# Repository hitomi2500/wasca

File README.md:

# wasca
wasca is a multipurpose Sega Saturn cartridge based on Lattice ECP5 FPGA with PicoRV32 RISC-V soft CPU core ([`picorv32`][2]). 

wasca can operate in several modes:

- Backup memory cartridge
- RAM expansion cartridge
- ROM cartridge
- Homebrew software compiled as a cartridge ROM 

> Netlink support is planned via an ESP32-CAM module connected to the 6-pin expansion header.

> Optical drive emulation (ODE) function is theoretically possible, but not planned currently.

> Profiling can be supported using a special firmware version, but it requires support from SH-2 code.

---

# Quick Start

1. Prepare the SD card formatted as FAT32. Other filesystems like NTFS and exFAT are not supported.
2. Copy `wasca.ss` and `wasca.rv` to the SD card root directory. Note that the file names should be in lowercase on the card, check FAT32 LFN support or reformat the card if they are not.
3. Insert the SD card into wasca, plug wasca into the cartridge slot, power on the console
4. Verify that the front LED on the cartridge turns red, then blue.
5. wasca menu should appear on screen after boot logo. Some ODEs can bypass wasca boot process entirely. In this case, consult your ODE documentation to learn how to return to cartridge boot mode after selecting a game.

---

# LED Status Reference

| Color | Meaning |
|---|---|
| Red | Reading SD card at startup or system error. |
| Red, blinking | Boot error, either `wasca.ss` and `wasca.rv` was not found on SD card, refer to on-screen error message. |
| Blue | Firmware found on SD card, boot successful, waiting for menu selection. |
| Green, blinking | Write access in RAM or Homebrew mode. |
| Magenta, blinking | Write access to backup memory in backup mode or filesystem write access. |
| Cyan, blinking | Massive write access to backup memory (happens during format) or filesystem read access. |
| Yellow, blinking | Preparing backup memory |
| White, blinking | Filesystem open, close, seek etc.|

---

# Backup Memory Support

wasca supports four backup memory sizes:

- 0.5 MB (official Sega Saturn size)
- 1 MB
- 2 MB
- 4 MB

If not already present, the following backup files are created automatically on the SD card when selected from the menu:

- `backup05.bin`
- `backup1.bin`
- `backup2.bin`
- `backup4.bin`

Syncronization is done automatically, led blinking with magenta color signals write access, led blinking with cyan signals massive write access and usually happens during cart format in BIOS.

---

# RAM Expansion Support

wasca supports these RAM expansion modes:

- 1 MB official RAM expansion (timings not 100% compatible)
- 4 MB official RAM expansion
- Heart of Darkness mode (HoD will work in homebrew mode as well)

---

# ROM Support

The following games require corresponding ROM files placed in the SD card root directory:

| Game | Required File |
|---|---|
| King of Fighters '95 | `kof95.bin` |
| Ultraman | `ultraman.bin` |

When present on SD card, ROM will appear in menu and should be selected prior to launching the game.

---

# Homebrew Support

Any Sega Saturn homebrew compiled for cartridge can be placed into the SD card root directory. `.ss` and `.bin` extensions are supported. wasca automatically scans and lists `.bin` and `.ss` files found in the SD card root directory.

In homebrew mode, wasca exposes:

- 32 MB of CS0 space
- 16 MB of CS1 space

These regions are available to the developer as RAM.

[`Yaul`][1] system library supports compiling sortware for cartridge with a special makefile include (build.post.ss.mk) that should be added to the project's Makefile instead of the default one (build.post.iso-cue.mk).

---

# Menu limit

Currently, wasca menu is limited to 18 items. If more `.bin` and `.ss` files that fit on screen are present in the SD card root, only first items will be shown. Use wasca commander (still under development) file manager to load extra files or files in non-root folders.

---

# Firmware update

wasca firmware consists of 3 parts:

- FPGA gateware: `attosoc.bit`
- RISC-V firmware: `wasca.rv`
- SH-2 firmware: `wasca.ss`

### Updating FPGA gateware

1. Disconnect wasca from the console
2. Remove two screws on the back of the cartridge
3. Open the cartridge shell
4. Connect wasca to PC using USB-C cable
5. A removable drive will appear
6. Copy `attosoc.bit` onto the drive
7. Wait for 2 minutes before disconnecting the cartridge
8. Assemble the cartridge and connect to the console.

### Updating RISC-V and SH-2 Firmware

1. Remove SD card from wasca
2. Replace the existing `wasca.rv` and `wasca.ss` files on the SD card with a newer version.
3. Re-insert the card. Console power cycle is necessary for wasca to load the new firmware.

---

# SD card removal
Removing the SD card when console is powered up is only recommended when the front LED is not lit and not blinking. Re-inserting the card without reset is possible if LED did not blink while the card was removed, but data integrity is not tested and not guaranteed.

---

# Troubleshooting

### Lit red LED and/or "wasca : boot error" on screen

Possible causes:
- Unsupported filesystem
- Bad SD card
- Unstable SD card connection

Try:
- Re-insert the SD card
- Reformat the SD card as FAT32
- Replace SD card

### Blinking red LED and/or missing file message on screen

Possible causes:
- Missing `wasca.ss` or `wasca.rv` in the SD card root
- Unsupported filesystem
- Bad SD card

Try:
- Verify that both `wasca.ss` and `wasca.rv` exists in the SD card root directory, named in lowercase
- Reformat the SD card as FAT32
- Replace the SD card

### Lit blue LED, wasca boot menu does not appear during boot

Possible causes:
- Poor cartridge connection
- Dirty cartridge connector
- ODE bypassing cartridge initialization

Try:
- Reseating the cartridge
- Cleaning the cartridge and connector
- Consulting your ODE documentation for cartridge boot instructions

### Game ROM of homebrew .ss file present in root folder, but does not appear in the menu

Possible causes:
- Too many files in SD card root
- Wrong charset

Try:
- Verify that there is enough place on the screen to print necessary menu item. If last menu item is 18, it's probably overfilled and extra items are not shown.
- Verify that the file extension is `.bin` or `.ss`, lowercase, latin1 characters.

[1]: https://github.com/ijacquez/libyaul
[2]: https://github.com/YosysHQ/picorv32

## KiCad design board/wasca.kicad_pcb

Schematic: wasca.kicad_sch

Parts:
C1, C2, C4, C5, C7, C9, C10, C11, C14, C15, C16, C17, C18, C19, C20, C21, C22, C23, C24, C25, C26, C27, C28, C33, C34, C35, C36, C37, C38, C39, C40, C46, C47, C48: 0.1uF; C_0603_1608Metric_Pad1.08x0.95mm_HandSolder; LCSC C1590
C3, C6, C8, C29: 4.7uF; C_0603_1608Metric_Pad1.08x0.95mm_HandSolder; LCSC C1705
C12, C13: 15pF; C_0603_1608Metric_Pad1.08x0.95mm_HandSolder; LCSC C1644
C30, C31: 22uF; C_0603_1608Metric_Pad1.08x0.95mm_HandSolder; LCSC C59461
C32, C41: 1uF; C_0603_1608Metric_Pad1.08x0.95mm_HandSolder; LCSC C1592
C42, C43: 18pF; C_0603_1608Metric_Pad1.08x0.95mm_HandSolder; LCSC C1647
C44, C45: 10uF; C_1206_3216Metric_Pad1.33x1.80mm_HandSolder; LCSC C1691
C49, C50, C51, C52, C53, C54, C55, C56, C57, C58, C59: 0.1uF; C_0402_1005Metric; LCSC C1525
CN1: UC09-0B16F00P11; DX07S016JA1R1500; LCSC C36936538
CN2: CARTRIDGE_EDGE_CONNECTOR; CARTRIDGE_EDGE_CONNECTOR2; not fitted
CN3: TFP09-2-12B; TFP09212B; Manufacturer_Part_Number TFP09-2-12B; not fitted
CN4: SD-CARD 11P; 693063020911; PART-NUMBER 693063020911; LCSC C7529393
CN5: 2.54-1*8P母环保; MODULE_ESP32-CAM-HALF; LCSC C27438
D1: BAT54C; SOT-23; LCSC C2135
D2: LED_RGB; LED_RGB_5050-6; not fitted
D3: LED_BKGR; LED_D5.0mm-4_RGB; LCSC C7371892
D4: LED; LED_0805; LCSC C965863
KICAD1: KICAD_LOGO; DESIGNED_WITH_KICAD_10X05; not fitted
L1, L2: 2.2uH; L_1008_2520Metric; LCSC C86092
R1, R4: 5.1K; R_0603_1608Metric_Pad0.98x0.95mm_HandSolder; LCSC C23186
R2, R19, R20: 1K; R_0603_1608Metric_Pad0.98x0.95mm_HandSolder; LCSC C21190
R3, R7, R8, R16, R17, R28: 0; R_0603_1608Metric_Pad0.98x0.95mm_HandSolder; LCSC C21189
R5, R6: 27; R_0603_1608Metric_Pad0.98x0.95mm_HandSolder; LCSC C25190
R9: 680K; R_0603_1608Metric_Pad0.98x0.95mm_HandSolder; LCSC C2907061
R10: 200K; R_0603_1608Metric_Pad0.98x0.95mm_HandSolder; LCSC C25811
R11, R14, R15: 470; R_0603_1608Metric_Pad0.98x0.95mm_HandSolder; LCSC C23179
R12: 150K; R_0603_1608Metric_Pad0.98x0.95mm_HandSolder; LCSC C22807
R13: 240K; R_0603_1608Metric_Pad0.98x0.95mm_HandSolder; LCSC C4197
R18, R35: 4K7; R_0603_1608Metric_Pad0.98x0.95mm_HandSolder; LCSC C23162
R21, R22, R29, R30, R31, R32, R33, R34, R36: 10K; R_0603_1608Metric_Pad0.98x0.95mm_HandSolder; LCSC C15401
R23, R24, R25, R26, R27: 33K; R_0603_1608Metric_Pad0.98x0.95mm_HandSolder; LCSC C4216
SEGATA1: LOGO; Segata_Sanshiro; not fitted
SHIRO!1: SHIRO_LOGO; SHIRO!; not fitted
SW1, SW2: TS-1101-C-W; SW_Tactile_SPST_NO_Straight_CK_PTS636Sx25SMTRLFS; LCSC C318938
TP1: TestPoint; TestPoint_Pad_D1.5mm; not fitted
TP2: 5VSAT; TestPoint_Pad_D1.5mm; not fitted
TP3: 5VSYS; TestPoint_Pad_D1.5mm; not fitted
TP4: 5VUSB; TestPoint_Pad_D1.5mm; not fitted
TP5: 2.5V; TestPoint_Pad_D1.5mm; not fitted
TP6: 3.3V; TestPoint_Pad_D1.5mm; not fitted
TP7: 1.1V; TestPoint_Pad_D1.5mm; not fitted
TP8: DONE; TestPoint_Pad_D1.0mm; not fitted
TP9: TCK; TestPoint_Pad_D1.0mm; not fitted
TP10: TDI; TestPoint_Pad_D1.0mm; not fitted
TP11: TMS; TestPoint_Pad_D1.0mm; not fitted
TP12: TDO; TestPoint_Pad_D1.0mm; not fitted
TP13, TP14: TestPoint; TestPoint_Pad_D1.0mm; not fitted
U1, U2, U4, U5, U6: SN74LVC1T45DBVR; SOT-23-6; LCSC C7843
U3, U17: P25Q16SH-SSH-IR; SOIC-8_5.3x5.3mm_P1.27mm; LCSC C7466814
U7, U8, U10: 74ALVC164245DGG:11-JSM; TSSOP-48_6.1x12.5mm_P0.5mm; LCSC C53436298
U9: RP2040; QFN-56-1EP_7x7mm_P0.4mm_EP3.2x3.2mm; LCSC C2040
U11, U12: W9825G6KH-6; TSOP-II-54_22.2x10.16mm_P0.8mm; LCSC C62246
U13, U14: SY8008CAAC; SOT23-5_SY8008B_SGY; LCSC C81889
U15: XC6206P252MR; SOT-23-3; LCSC C15906
U16: LFE5U-25F-6BG256I; caBGA256_LAT; LCSC C1521614
VACHE1: LOGO; LOGO_VACHE_SIM; not fitted
Y1: X322512MSB4SI; Crystal_SMD_3225-4Pin_3.2x2.5mm; LCSC C9002
Y2: SX2M25.000M20F30TNN; Oscillator_SMD_SeikoEpson_SG210-4Pin_2.5x2.0mm_HandSoldering; LCSC C2901601

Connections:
/5V_SATURN_DETECT: R35.2, R36.1, U16.J13 (PR17C)
/+1_1V: C54.1, C56.1, C58.1, R17.2, U16.G6 (VCC), U16.G7 (VCC), U16.G9 (VCC), U16.L8 (VCC), U16.L9 (VCC), U16.L10 (VCC)
/+1_1V_RPI: C22.1, C24.1, C26.1, TP1.1 (1_1), U9.23 (DVDD), U9.45 (VREG_VOUT), U9.50 (DVDD)
/+2_5V: C49.1, C50.1, R8.2, U16.G11 (VCCAUX), U16.L7 (VCCAUX)
/+3_3V: C4.1, C5.1, C7.1, C17.1, C18.1, C19.1, C20.1, C21.1, C23.1, C25.1, C27.1, C28.1, C33.1, C34.1, C35.1, C36.1, C37.1, C38.1, C39.1, C40.1, C46.1, C48.1, C51.1, C52.1, C53.1, C55.1, C57.1, C59.1, CN3.4 (VDD), CN4.4 (VDD), R7.2, R16.2, R19.2, R21.1, R22.1, R23.1, R24.1, R25.1, R26.1, R27.1, R28.1, R29.1, R30.1, R31.1, R32.1, R33.1, R34.1, U1.1 (VCCA), U2.1 (VCCA), U3.8 (VCC), U4.1 (VCCA), U4.5 (DIR), U5.1 (VCCA), U5.5 (DIR), U6.1 (VCCA), U6.5 (DIR), U7.31 (VCCA), U7.42 (VCCA), U8.31 (VCCA), U8.42 (VCCA), U9.1 (IOVDD), U9.10 (IOVDD), U9.22 (IOVDD), U9.33 (IOVDD), U9.42 (IOVDD), U9.44 (VREG_VIN), U9.48 (USB_VDD), U9.49 (IOVDD), U10.31 (VCCA), U10.42 (VCCA), U11.1 (VDD), U11.3 (VDDQ), U11.9 (VDDQ), U11.14 (VDD), U11.27 (VDD), U11.43 (VDDQ), U11.49 (VDDQ), U12.1 (VDD), U12.3 (VDDQ), U12.9 (VDDQ), U12.14 (VDD), U12.27 (VDD), U12.43 (VDDQ), U12.49 (VDDQ), U16.F6 (VCCIO0), U16.F7 (VCCIO0), U16.F10 (VCCIO1), U16.F11 (VCCIO1), U16.H6 (VCCIO7), U16.H7 (VCCIO7), U16.H11 (VCCIO2), U16.J6 (VCCIO6), U16.J7 (VCCIO6), U16.J11 (VCCIO2), U16.K11 (VCCIO3), U16.L6 (VCCIO8), U16.L11 (VCCIO3), U16.P10 (CFG_1), U17.8 (VCC), Y2.4 (Vcc)
/+5V_SATURN: C1.1, C2.1, C3.1, C8.1, C9.1, C10.1, C11.1, C14.1, C15.1, C16.1, CN2.A1 (VCC), CN2.A2 (VCC), CN2.A27 (VCC), CN2.A67 (VCC), CN2.B1 (VCC), CN2.B2 (VCC), CN2.B27 (VCC), CN2.B67 (VCC), D1.1, R35.1, TP2.1 (1_1), U1.6 (VCCB), U2.6 (VCCB), U4.6 (VCCB), U5.6 (VCCB), U6.6 (VCCB), U7.7 (VCCB), U7.18 (VCCB), U8.7 (VCCB), U8.18 (VCCB), U10.7 (VCCB), U10.18 (VCCB)
/+5V_SYS: C29.1, C30.1, C31.1, C32.1, C47.1, CN5.1 (5V), D1.3, TP3.1 (1_1), U13.1 (EN), U13.4 (IN), U14.1 (EN), U14.4 (IN), U15.3 (VI)
/+5V_USB: C6.1, CN1.A4 (VBUS), CN1.A9 (VBUS), CN1.B4 (VBUS), CN1.B9 (VBUS), D1.2, TP4.1 (1_1)
/ABUS_3V_A1: U10.43 (1A3), U16.J14 (PR20C)
/ABUS_3V_A2: U7.30 (2A4), U16.T6 (PB4A)
/ABUS_3V_A3: U7.32 (2A3), U16.P5 (PL47D)
/ABUS_3V_A4: U7.33 (2A2), U16.R5 (PL44A)
/ABUS_3V_A5: U7.35 (2A1), U16.T4 (PL44B)
/ABUS_3V_A6: U7.36 (2A0), U16.R4 (PL41C)
/ABUS_3V_A7: U7.37 (1A7), U16.T3 (PL41D)
/ABUS_3V_A8: U10.37 (1A7), U16.N13 (PR38A)
/ABUS_3V_A9: U10.38 (1A6), U16.L13 (PR29C)
/ABUS_3V_A10: U10.41 (1A4), U16.K14 (PR20D)
/ABUS_3V_A11: U10.40 (1A5), U16.L14 (PR32C)
/ABUS_3V_A12: U10.35 (2A1), U16.P11 (PR47C)
/ABUS_3V_A13: U10.36 (2A0), U16.N12 (PR44D)
/ABUS_3V_A14: U7.38 (1A6), U16.R3 (PL41B)
/ABUS_3V_A15: U10.33 (2A2), U16.N6 (PL47B)
/ABUS_3V_A16: U7.40 (1A5), U16.T2 (PL38D)
/ABUS_3V_A17: U10.32 (2A3), U16.N5 (PL44D)
/ABUS_3V_A18: U7.41 (1A4), U16.P3 (PL38B)
/ABUS_3V_A19: U10.30 (2A4), U16.P4 (PL41A)
/ABUS_3V_A20: U7.43 (1A3), U16.R2 (PL38C)
/ABUS_3V_A21: U10.29 (2A5), U16.N4 (PL38A)
/ABUS_3V_A22: U7.44 (1A2), U16.R1 (PL35B)
/ABUS_3V_A23: U10.27 (2A6), U16.M4 (PL35C)
/ABUS_3V_A24: U7.46 (1A1), U16.P2 (PL32B)
/ABUS_3V_CS0: U10.44 (1A2), U16.H14 (PR14D)
/ABUS_3V_CS1: U7.27 (2A6), U16.R7 (PB6A)
/ABUS_3V_CS2: U10.46 (1A1), U16.G14 (PR14C)
/ABUS_3V_D0: U8.47 (1A0), U16.E13 (PT62B)
/ABUS_3V_D1: U8.46 (1A1), U16.D14 (PR2D)
/ABUS_3V_D2: U8.44 (1A2), U16.C13 (PT60B)
/ABUS_3V_D3: U8.43 (1A3), U16.R12 (PR44A)
/ABUS_3V_D4: U8.32 (2A3), U16.R15 (PR38C)
/ABUS_3V_D5: U8.33 (2A2), U16.T15 (PR38D)
/ABUS_3V_D6: U8.35 (2A1), U16.R14 (PR41B)
/ABUS_3V_D7: U8.36 (2A0), U16.T14 (PR41D)
/ABUS_3V_D8: U8.41 (1A4), U16.P12 (PR47D)
/ABUS_3V_D9: U8.40 (1A5), U16.R13 (PR41C)
/ABUS_3V_D10: U8.38 (1A6), U16.T13 (PR44B)
/ABUS_3V_D11: U8.37 (1A7), U16.P13 (PR41A)
/ABUS_3V_D12: U8.26 (2A7), U16.P16 (PR35A)
/ABUS_3V_D13: U8.27 (2A6), U16.P15 (PR32B)
/ABUS_3V_D14: U8.29 (2A5), U16.R16 (PR35B)
/ABUS_3V_D15: U8.30 (2A4), U16.P14 (PR38B)
/ABUS_3V_IRQ: U1.3 (A), U16.J3 (PL20C)
/ABUS_3V_MUX_DATA_DIR: U8.1 (1DIR), U8.24 (2DIR), U16.H4 (PL17B)
/ABUS_3V_RD: U7.29 (2A5), U16.R6 (PB4B)
/ABUS_3V_WR0: U10.47 (1A0), U16.F14 (PR5D)
/ABUS_3V_WR1: U7.26 (2A7), U16.R8 (PB13A)
/ABUS_A1: CN2.A45 (AA1), U10.6 (1B3)
/ABUS_A2: CN2.B44 (AA2), U7.19 (2B4)
/ABUS_A3: CN2.B43 (AA3), U7.17 (2B3)
/ABUS_A4: CN2.B42 (AA4), U7.16 (2B2)
/ABUS_A5: CN2.B40 (AA5), U7.14 (2B1)
/ABUS_A6: CN2.B39 (AA6), U7.13 (2B0)
/ABUS_A7: CN2.B38 (AA7), U7.12 (1B7)
/ABUS_A8: CN2.A40 (AA8), U10.12 (1B7)
/ABUS_A9: CN2.A42 (AA9), U10.11 (1B6)
/ABUS_A10: CN2.A44 (AA10), U10.8 (1B4)
/ABUS_A11: CN2.A43 (AA11), U10.9 (1B5)
/ABUS_A12: CN2.A38 (AA12), U10.14 (2B1)
/ABUS_A13: CN2.A39 (AA13), U10.13 (2B0)
/ABUS_A14: CN2.B37 (AA14), U7.11 (1B6)
/ABUS_A15: CN2.A37 (AA15), U10.16 (2B2)
/ABUS_A16: CN2.B35 (AA16), U7.9 (1B5)
/ABUS_A17: CN2.A35 (AA17), U10.17 (2B3)
/ABUS_A18: CN2.B34 (AA18), U7.8 (1B4)
/ABUS_A19: CN2.A34 (AA19), U10.19 (2B4)
/ABUS_A20: CN2.B33 (AA20), U7.6 (1B3)
/ABUS_A21: CN2.A33 (AA21), U10.20 (2B5)
/ABUS_A22: CN2.B32 (AA22), U7.5 (1B2)
/ABUS_A23: CN2.A32 (AA23), U10.22 (2B6)
/ABUS_A24: CN2.B31 (AA24), U7.3 (1B1)
/ABUS_CS0: CN2.A47 (ACS0), U10.5 (1B2)
/ABUS_CS1: CN2.B48 (ACS1), U7.22 (2B6)
/ABUS_CS2: CN2.A48 (ACS2), U10.3 (1B1)
/ABUS_D0: CN2.A55 (AD0), U8.2 (1B0)
/ABUS_D1: CN2.A56 (AD1), U8.3 (1B1)
/ABUS_D2: CN2.A57 (AD2), U8.5 (1B2)
/ABUS_D3: CN2.A58 (AD3), U8.6 (1B3)
/ABUS_D4: CN2.B58 (AD4), U8.17 (2B3)
/ABUS_D5: CN2.B57 (AD5), U8.16 (2B2)
/ABUS_D6: CN2.B56 (AD6), U8.14 (2B1)
/ABUS_D7: CN2.B55 (AD7), U8.13 (2B0)
/ABUS_D8: CN2.A60 (AD8), U8.8 (1B4)
/ABUS_D9: CN2.A61 (AD9), U8.9 (1B5)
/ABUS_D10: CN2.A62 (AD10), U8.11 (1B6)
/ABUS_D11: CN2.A63 (AD11), U8.12 (1B7)
/ABUS_D12: CN2.B63 (AD12), U8.23 (2B7)
/ABUS_D13: CN2.B62 (AD13), U8.22 (2B6)
/ABUS_D14: CN2.B61 (AD14), U8.20 (2B5)
/ABUS_D15: CN2.B60 (AD15), U8.19 (2B4)
/ABUS_IRQ: CN2.B53 (AIRQ), U1.4 (B)
/ABUS_RD: CN2.B47 (ARD), U7.20 (2B5)
/ABUS_WR0: CN2.A49 (AWR0), U10.2 (1B0)
/ABUS_WR1: CN2.B49 (AWR1), U7.23 (2B7)
/BUFFERS_OE: U7.25 (2OE), U7.48 (1OE), U8.25 (2OE), U8.48 (1OE), U10.25 (2OE), U10.48 (1OE), U16.L3 (PL32C)
/CLK_25M: U16.P6 (PL47C), Y2.3 (OUT)
/ESP32_CS: CN5.5 (IO15), U16.C6 (PT22A)
/ESP32_MISO: CN5.3 (IO12), U16.E7 (PT24A)
/ESP32_MOSI: CN5.4 (IO13), U16.D6 (PT20B)
/ESP32_SCK: CN5.6 (IO14), U16.C7 (PT27A)
/FPGA_QSPI_CLK: R30.2, U9.5 (GPIO3), U16.N9 (CCLK), U17.6 (CLK)
/FPGA_QSPI_CS: R29.2, U9.9 (GPIO7), U16.N8 (PB15A), U17.1 (~CS)
/FPGA_QSPI_D0: R31.2, U9.7 (GPIO5), U16.T8 (PB11B), U17.5 (DI/IO_{0})
/FPGA_QSPI_D1: R32.2, U9.12 (GPIO9), U16.T7 (PB11A), U17.2 (DO/IO_{1})
/FPGA_QSPI_D2: R33.2, U9.14 (GPIO11), U16.M7 (PB9B), U17.3 (~WP/IO_{2})
/FPGA_QSPI_D3: R34.2, U9.3 (GPIO1), U16.N7 (PB9A), U17.7 (~HOLD/~RESET/IO_{3})
/IBCK: CN2.A5 (IBCK), U5.4 (B)
/IBCK_3V: U5.3 (A), U16.F4 (PL8C)
/ILRCK: CN2.A6 (ILRCK), U6.4 (B)
/ILRCK_3V: U6.3 (A), U16.P8 (PB13B)
/IRQ_OUT_ENABLE: U1.5 (DIR), U16.F3 (PL5D)
/ISD: CN2.A4 (ISD), U4.4 (B)
/ISD_3V: U4.3 (A), U16.E3 (PL5C)
/JTAG_TCK: R18.2, TP9.1 (1_1), U16.T10 (TCK)
/JTAG_TDI: TP10.1 (1_1), U16.R11 (TDI)
/JTAG_TDO: TP12.1 (1_1), U16.M10 (TDO)
/JTAG_TMS: TP11.1 (1_1), U16.T11 (TMS)
/LEDB: R15.1, U16.D7 (PT24B)
/LEDG: R14.1, U16.E8 (PT33A)
/LEDR: R11.1, U16.E9 (PT40B)
/PROGRAMN: R21.2, SW2.2, U9.29 (GPIO18), U16.R9 (PROGRAMN)
/RESET: CN2.A3 (SYSRES), U10.23 (2B7)
/RESET_3V: U10.26 (2A7), U16.K4 (PL29A)
/RP_QSPI_CLK: U3.6 (CLK), U9.52 (QSPI_SCLK)
/RP_QSPI_CS: R2.2, U3.1 (~CS), U9.56 (~QSPI_SS)
/RP_QSPI_D0: U3.5 (DI/IO_{0}), U9.53 (QSPI_SD0)
/RP_QSPI_D1: U3.2 (DO/IO_{1}), U9.55 (QSPI_SD1)
/RP_QSPI_D2: U3.3 (~WP/IO_{2}), U9.54 (QSPI_SD2)
/RP_QSPI_D3: U3.7 (~HOLD/~RESET/IO_{3}), U9.51 (QSPI_SD3)
/SCSPCLK: CN2.A7 (SCSPCLK), U7.2 (1B0)
/SCSPCLK_3V: U7.47 (1A0), U16.G3 (PL14C)
/SDRAM1_A0: U11.23 (A0), U16.B8 (PT35B)
/SDRAM1_A1: U11.24 (A1), U16.A9 (PT42A)
/SDRAM1_A2: U11.25 (A2), U16.B9 (PT38A)
/SDRAM1_A3: U11.26 (A3), U16.A10 (PT42B)
/SDRAM1_A4: U11.29 (A4), U16.J16 (PR23A)
/SDRAM1_A5: U11.30 (A5), U16.K15 (PR23D)
/SDRAM1_A6: U11.31 (A6), U16.K16 (PR23C)
/SDRAM1_A7: U11.32 (A7), U16.L15 (PR26B)
/SDRAM1_A8: U11.33 (A8), U16.L16 (PR26A)
/SDRAM1_A9: U11.34 (A9), U16.M14 (PR32D)
/SDRAM1_A10: U11.22 (A10), U16.B10 (PT44A)
/SDRAM1_A11: U11.35 (A11), U16.M16 (PR26C)
/SDRAM1_A12: U11.36 (A12), U16.M15 (PR26D)
/SDRAM1_BA0: U11.20 (BA0), U16.B11 (PT49A)
/SDRAM1_BA1: U11.21 (BA1), U16.A11 (PT53A)
/SDRAM1_CAS: U11.17 (~CAS), U16.A13 (PT65A)
/SDRAM1_CKE: U11.37 (CKE), U16.N16 (PR32A)
/SDRAM1_CLK: U11.38 (CLK), U16.N14 (PR35D)
/SDRAM1_CS: U11.19 (~CS), U16.A12 (PT53B)
/SDRAM1_DQ0: U11.2 (DQ0), U16.E14 (PR5C)
/SDRAM1_DQ1: U11.4 (DQ1), U16.C16 (PR5A)
/SDRAM1_DQ2: U11.5 (DQ2), U16.C15 (PR5B)
/SDRAM1_DQ3: U11.7 (DQ3), U16.B16 (PR2A)
/SDRAM1_DQ4: U11.8 (DQ4), U16.B15 (PR2B)
/SDRAM1_DQ5: U11.10 (DQ5), U16.C14 (PR2C)
/SDRAM1_DQ6: U11.11 (DQ6), U16.A15 (PT67B)
/SDRAM1_DQ7: U11.13 (DQ7), U16.B14 (PT67A)
/SDRAM1_DQ8: U11.42 (DQ8), U16.H15 (PR20B)
/SDRAM1_DQ9: U11.44 (DQ9), U16.G16 (PR20A)
/SDRAM1_DQ10: U11.45 (DQ10), U16.G15 (PR14B)
/SDRAM1_DQ11: U11.47 (DQ11), U16.F16 (PR14A)
/SDRAM1_DQ12: U11.48 (DQ12), U16.F15 (PR11C)
/SDRAM1_DQ13: U11.50 (DQ13), U16.E16 (PR11D)
/SDRAM1_DQ14: U11.51 (DQ14), U16.E15 (PR8B)
/SDRAM1_DQ15: U11.53 (DQ15), U16.D16 (PR8A)
/SDRAM1_DQM0: U11.15 (DQML), U16.A14 (PT65B)
/SDRAM1_DQM1: U11.39 (DQMH), U16.J15 (PR23B)
/SDRAM1_RAS: U11.18 (~RAS), U16.B12 (PT56A)
/SDRAM1_WE: U11.16 (~WE), U16.B13 (PT60A)
/SDRAM2_A0: U12.23 (A0), U16.K1 (PL23C)
/SDRAM2_A1: U12.24 (A1), U16.J2 (PL23B)
/SDRAM2_A2: U12.25 (A2), U16.J1 (PL23A)
/SDRAM2_A3: U12.26 (A3), U16.H2 (PL20B)
/SDRAM2_A4: U12.29 (A4), U16.B6 (PT22B)
/SDRAM2_A5: U12.30 (A5), U16.A7 (PT29A)
/SDRAM2_A6: U12.31 (A6), U16.B7 (PT27B)
/SDRAM2_A7: U12.32 (A7), U16.A8 (PT29B)
/SDRAM2_A8: U12.33 (A8), U16.A6 (PT18B)
/SDRAM2_A9: U12.34 (A9), U16.B5 (PT15B)
/SDRAM2_A10: U12.22 (A10), U16.K2 (PL23D)
/SDRAM2_A11: U12.35 (A11), U16.A5 (PT18A)
/SDRAM2_A12: U12.36 (A12), U16.C5 (PT15A)
/SDRAM2_BA0: U12.20 (BA0), U16.L2 (PL26B)
/SDRAM2_BA1: U12.21 (BA1), U16.L1 (PL26A)
/SDRAM2_CAS: U12.17 (~CAS), U16.N1 (PL32A)
/SDRAM2_CKE: U12.37 (CKE), U16.A4 (PT6B)
/SDRAM2_CLK: U12.38 (CLK), U16.B4 (PT11B)
/SDRAM2_CS: U12.19 (~CS), U16.M1 (PL26C)
/SDRAM2_DQ0: U12.2 (DQ0), U16.D1 (PL8A)
/SDRAM2_DQ1: U12.4 (DQ1), U16.D3 (PL2D)
/SDRAM2_DQ2: U12.5 (DQ2), U16.E1 (PL11D)
/SDRAM2_DQ3: U12.7 (DQ3), U16.E2 (PL8B)
/SDRAM2_DQ4: U12.8 (DQ4), U16.F1 (PL14A)
/SDRAM2_DQ5: U12.10 (DQ5), U16.F2 (PL11C)
/SDRAM2_DQ6: U12.11 (DQ6), U16.G1 (PL20A)
/SDRAM2_DQ7: U12.13 (DQ7), U16.G2 (PL14B)
/SDRAM2_DQ8: U12.42 (DQ8), U16.C4 (PT11A)
/SDRAM2_DQ9: U12.44 (DQ9), U16.A2 (PT4A)
/SDRAM2_DQ10: U12.45 (DQ10), U16.B3 (PT4B)
/SDRAM2_DQ11: U12.47 (DQ11), U16.B2 (PL2B)
/SDRAM2_DQ12: U12.48 (DQ12), U16.B1 (PL2A)
/SDRAM2_DQ13: U12.50 (DQ13), U16.C3 (PL2C)
/SDRAM2_DQ14: U12.51 (DQ14), U16.C1 (PL5A)
/SDRAM2_DQ15: U12.53 (DQ15), U16.C2 (PL5B)
/SDRAM2_DQM0: U12.15 (DQML), U16.P1 (PL35A)
/SDRAM2_DQM1: U12.39 (DQMH), U16.A3 (PT6A)
/SDRAM2_RAS: U12.18 (~RAS), U16.M2 (PL26D)
/SDRAM2_WE: U12.16 (~WE), U16.N3 (PL35D)
/SD_CLK: CN3.5 (CLK), CN4.5 (CLK), U16.E11 (PT51B)
/SD_CMD: CN3.3 (CMD), CN4.2 (CMD), R25.2, U16.C9 (PT38B)
/SD_DAT0: CN3.7 (DAT0), CN4.7 (DAT0), R24.2, U16.C11 (PT49B)
/SD_DAT1: CN3.8 (DAT1), CN4.8 (DAT1), R23.2, U16.D12 (PT58A)
/SD_DAT2: CN3.1 (DAT2), CN4.9 (DAT2), R27.2, U16.D8 (PT33B)
/SD_DAT3: CN3.2 (DAT3/CD), CN4.1 (CD/DAT3), R26.2, U16.D10 (PT47A)
/SD_DET_A: CN3.10 (GND), CN4.CD, U16.C12 (PT56B)
/SD_DET_B: CN3.9 (CARD_DETECTION), U16.E10 (PT47B)
/SSEL: CN2.B3 (SSEL), U2.4 (B)
/SSEL_3V: R3.1, U16.D4 (PT9B)
/USB_DM: CN1.A7 (D-), CN1.B7 (D-), R5.1
/USB_DP: CN1.A6 (D+), CN1.B6 (D+), R6.1
GND: C1.2, C2.2, C3.2, C4.2, C5.2, C6.2, C7.2, C8.2, C9.2, C10.2, C11.2, C12.2, C13.1, C14.2, C15.2, C16.2, C17.2, C18.2, C19.2, C20.2, C21.2, C22.2, C23.2, C24.2, C25.2, C26.2, C27.2, C28.2, C29.2, C30.2, C31.2, C32.2, C33.2, C34.2, C35.2, C36.2, C37.2, C38.2, C39.2, C40.2, C41.2, C44.2, C45.2, C46.2, C47.2, C48.2, C49.2, C50.2, C51.2, C52.2, C53.2, C54.2, C55.2, C56.2, C57.2, C58.2, C59.2, CN1.A1 (GND), CN1.A12 (GND), CN1.B1 (GND), CN1.B12 (GND), CN1.SH (SHIELD), CN2.A8 (GND), CN2.A13 (GND), CN2.A18 (GND), CN2.A23 (GND), CN2.A29 (GND), CN2.A36 (GND), CN2.A41 (GND), CN2.A46 (GND), CN2.A54 (GND), CN2.A59 (GND), CN2.A64 (GND), CN2.A65 (GND), CN2.B7 (GND), CN2.B8 (GND), CN2.B13 (GND), CN2.B18 (GND), CN2.B23 (GND), CN2.B29 (GND), CN2.B36 (GND), CN2.B41 (GND), CN2.B46 (GND), CN2.B54 (GND), CN2.B59 (GND), CN2.B64 (GND), CN2.B65 (GND), CN3.6 (VSS), CN3.11 (SHIELD), CN3.12 (SHIELD), CN3.13 (SHIELD), CN4.3 (VSS1), CN4.6 (VSS2), CN4.S1, CN4.S2, CN4.S3, CN4.S4, CN5.2 (GND), D2.1 (RK), D2.2 (GK), D2.3 (BK), D3.2 (K), D4.1 (K), R1.2, R4.2, R12.1, R13.1, R18.1, R36.2, SW1.1, SW2.1, U1.2 (GND), U2.2 (GND), U2.5 (DIR), U3.4 (GND), U4.2 (GND), U5.2 (GND), U6.2 (GND), U7.1 (1DIR), U7.4 (GND), U7.10 (GND), U7.15 (GND), U7.21 (GND), U7.24 (2DIR), U7.28 (GND), U7.34 (GND), U7.39 (GND), U7.45 (GND), U8.4 (GND), U8.10 (GND), U8.15 (GND), U8.21 (GND), U8.28 (GND), U8.34 (GND), U8.39 (GND), U8.45 (GND), U9.19 (TESTEN), U9.57 (GND), U10.1 (1DIR), U10.4 (GND), U10.10 (GND), U10.15 (GND), U10.21 (GND), U10.24 (2DIR), U10.28 (GND), U10.34 (GND), U10.39 (GND), U10.45 (GND), U11.6 (VSSQ), U11.12 (VSSQ), U11.28 (VSS), U11.41 (VSS), U11.46 (VSSQ), U11.52 (VSSQ), U11.54 (VSS), U12.6 (VSSQ), U12.12 (VSSQ), U12.28 (VSS), U12.41 (VSS), U12.46 (VSSQ), U12.52 (VSSQ), U12.54 (VSS), U13.2 (GND), U14.2 (GND), U15.1 (GND), U16.A1 (GND), U16.A16 (GND), U16.D2 (GND), U16.D15 (GND), U16.F8 (GND), U16.F9 (GND), U16.G8 (GND), U16.G10 (GND), U16.H1 (GND), U16.H8 (GND), U16.H9 (GND), U16.H10 (GND), U16.H16 (GND), U16.J8 (GND), U16.J9 (GND), U16.J10 (GND), U16.K6 (GND), U16.K7 (GND), U16.K8 (GND), U16.K9 (GND), U16.K10 (GND), U16.N2 (GND), U16.N10 (CFG_0), U16.N15 (GND), U16.R10 (CFG_2), U16.T1 (GND), U16.T5 (GND), U16.T12 (GND), U16.T16 (GND), U17.4 (GND), Y1.2 (G), Y1.4 (G), Y2.2 (GND)
unnamed: C42.1, C44.1, L1.2, R9.1, R16.1, TP6.1 (1_1)
unnamed: C43.1, C45.1, L2.2, R10.1, R17.1, TP7.1 (1_1)
unnamed: CN1.A5 (CC1), R1.1
unnamed: CN1.B5 (CC2), R4.1
unnamed: D2.4 (BA), D3.1 (BA), R15.2
unnamed: D2.5 (GA), D3.3 (GA), R14.2
unnamed: D2.6 (RA), D3.4 (RA), R11.2
unnamed: D4.2 (A), R20.1
unnamed: R2.1, SW1.2
unnamed: R3.2, U2.3 (A)
unnamed: R7.1, U9.43 (ADC_AVDD)
unnamed: TP13.1 (1_1), U9.34 (GPIO22)
unnamed: TP14.1 (1_1), U9.37 (GPIO25)
unnamed: R5.2, U9.46 (USB_DM)
unnamed: R6.2, U9.47 (USB_DP)
unnamed: C12.1, U9.20 (XIN), Y1.3
unnamed: C13.2, U9.21 (XOUT), Y1.1
unnamed: C42.2, R9.2, R12.2, U13.5 (FB)
unnamed: L1.1, U13.3 (LX)
unnamed: C43.2, R10.2, R13.2, U14.5 (FB)
unnamed: L2.1, U14.3 (LX)
unnamed: C41.1, R8.1, TP5.1 (1_1), U15.2 (VO)
unnamed: R19.1, R20.2, TP8.1 (1_1), U16.P9 (DONE)
unnamed: R22.2, U16.T9 (INITN)
unnamed: R28.2, Y2.1 (OE)

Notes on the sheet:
--- Changelog --- V1.0 hitomi2500 : - Initial version with 10M04SFE, SDRAM, FT201XS V1.1 hitomi2500 : - Both DDR/SDRAM support - Added USB and bluetooth support - Sound I/O mapped to MAX10 V1.2 cafe-alpha : - Changed PCB shape and ICs position in order to fit Action Replay case - Changed MAX10 chip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
PROGRAM PICO
Compatible connectors: Hroparts TF-01A SOFNG TF-15x15 SOFNG TF-015 XUNPU TF-115K XUNPU TF-109 HOAUC HYC77-TF09-200
Compatible connectors: JAE DX07S016JA1R1500 JAE DX07S016JA3R1500 HROPARTS TYPE-C-31-M-12 HROPARTS TYPE-C-31-M-14 XKB U262-161N-4BVC11 Jing Ext. C167321
ONLY 1 OF THE RGB LEDS SHOULD BE PLACED
Partially compatible (signals only) Hirose DM3AT-SF-PEJM5 Kyocera 045138008100858+ Yamaichi PJS008-4100-0-VE

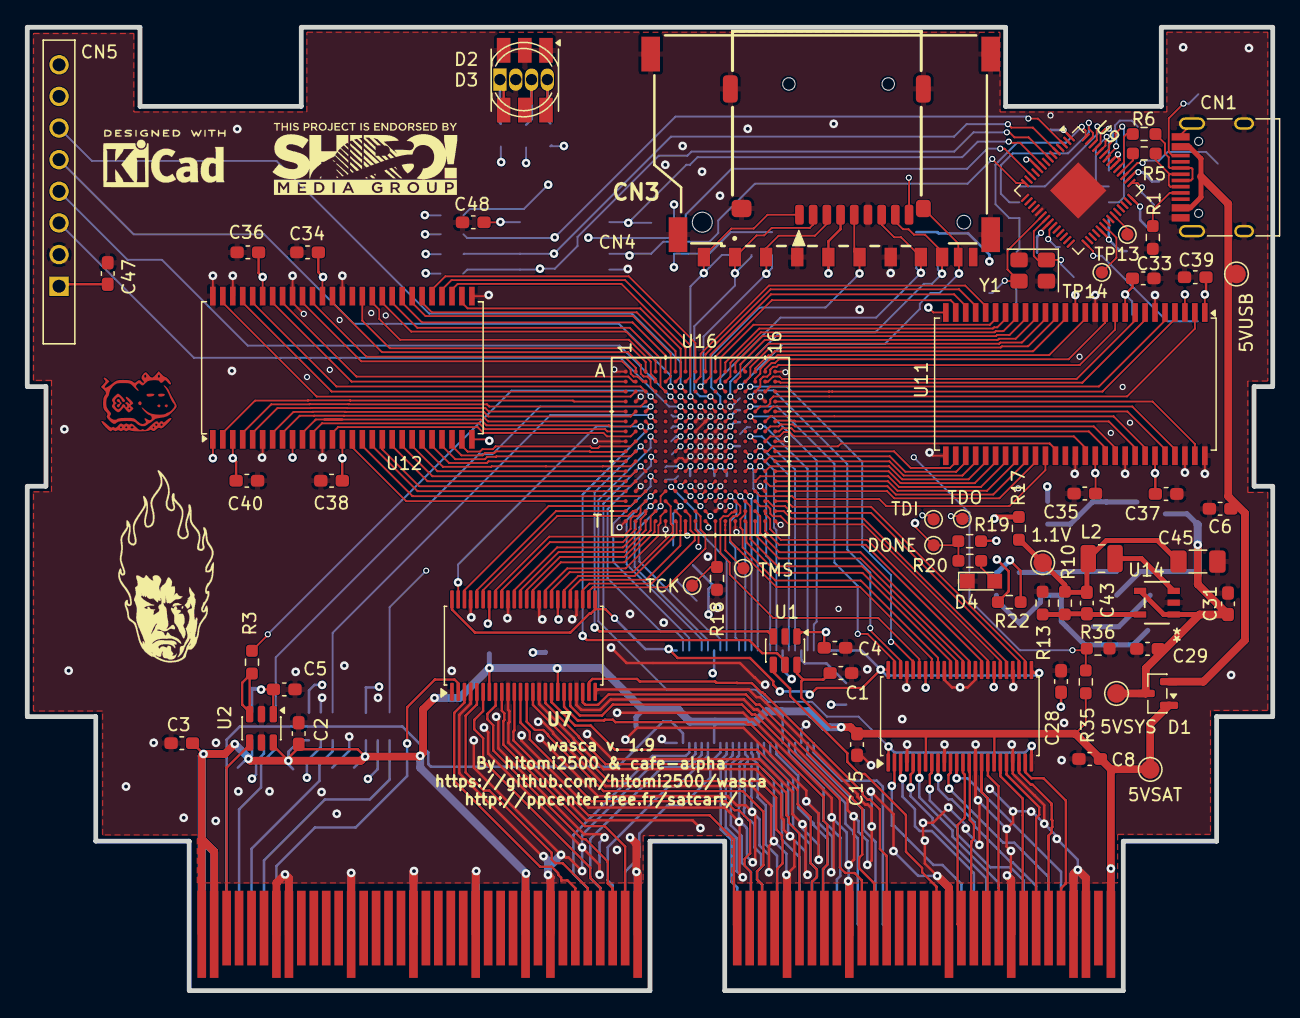
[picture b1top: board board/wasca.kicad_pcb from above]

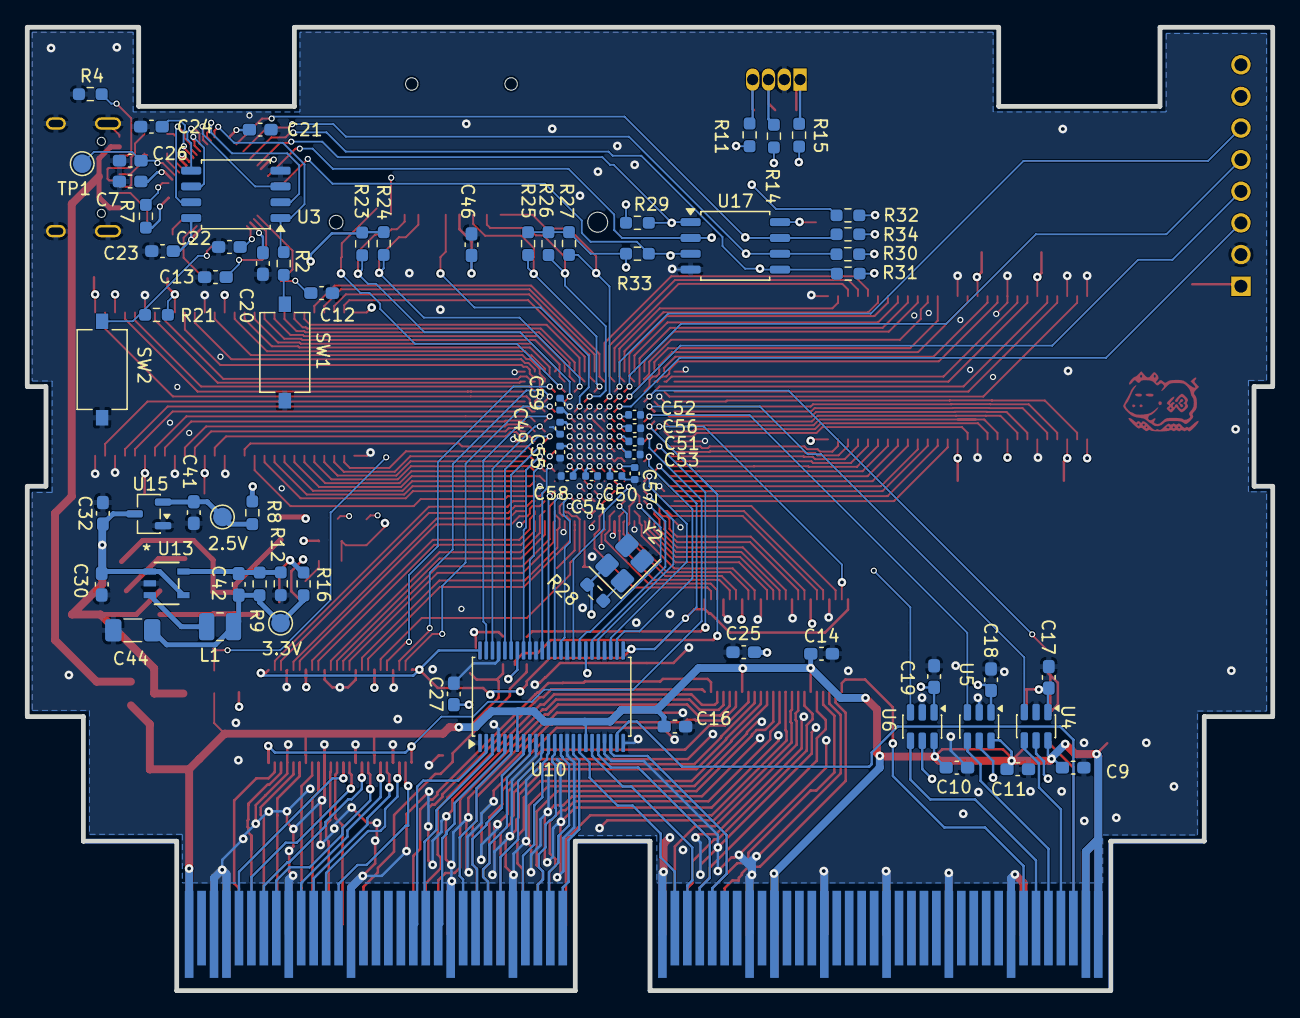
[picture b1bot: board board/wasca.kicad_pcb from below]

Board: 4 copper layers, 100.0 x 77.4 mm, 145 parts (74 on the bottom side), 256 nets.

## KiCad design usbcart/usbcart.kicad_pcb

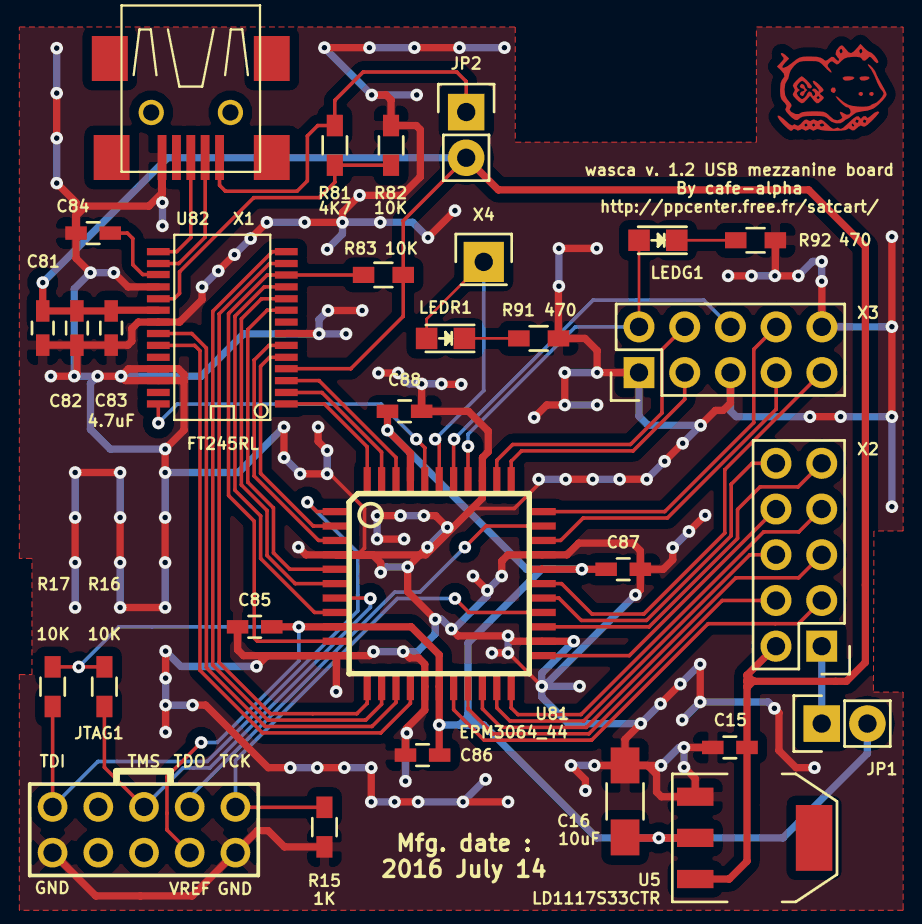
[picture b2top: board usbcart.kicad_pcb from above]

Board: 2 copper layers, 30 parts (0 on the bottom side), 45 nets.

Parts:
C15, C81, C82, C84, C85, C86, C87, C88: 0.1uF; C_0603_HandSoldering
C16: 10uF; C_1206_HandSoldering
C83: 4.7uF; C_0603_HandSoldering
JP1, JP2: JUMPER; Pin_Header_Straight_1x02
JTAG1: AVR-JTAG-10; JTAG_Header
LEDG1: LED; LED_0805
LEDR1: LED; LED_0805
R15: 1K; R_0603_HandSoldering
R16, R17, R82, R83: 10K; R_0603_HandSoldering
R81: 4K7; R_0603_HandSoldering
R91, R92: 470; R_0603_HandSoldering
U5: LD1117S33CTR; SOT-223
U81: EPM3064_44; TQFP44
U82: FT245RL; SSOP28
X1: USB-MB-S; con-usb-USB-MB-S
X2, X3: CONN_02X05; Pin_Header_Straight_2x05
X4: CONN_01X01; Pin_Header_Straight_1x01

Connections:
/+3_3V: C16.1, C85.1, C86.1, C87.1, C88.1, JP1.2, JTAG1.4, R16.1, R17.1, U5.2, U81.9, U81.17, U81.29, U81.41
/+3_3V_BOARD: JP1.1, X2.1
/+5V: C15.1, C81.1, C82.1, C83.1, JP2.2, R83.1, U5.3, U82.4, U82.20, X2.2
/ABUS_A0: U81.31, X3.7
/ABUS_A1: U81.22, X2.7
/ABUS_A2: U81.33, X3.8
/ABUS_D0: U81.21, X2.6
/ABUS_D1: U81.20, X2.5
/ABUS_D2: U81.19, X2.4
/ABUS_D3: U81.18, X2.3
/ABUS_D4: U81.23, X2.8
/ABUS_D5: U81.25, X2.9
/ABUS_D6: U81.27, X2.10
/ABUS_D7: U81.28, X3.9
/EPM_SPARE: LEDR1.2, U81.39, X4.1
/FTDI_D0: U81.44, U82.1
/FTDI_D1: U81.2, U82.5
/FTDI_D2: U81.42, U82.3
/FTDI_D3: U81.8, U82.11
/FTDI_D4: U81.43, U82.2
/FTDI_D5: U81.5, U82.9
/FTDI_D6: U81.6, U82.10
/FTDI_D7: U81.3, U82.6
/FTDI_OSCO: U81.40, U82.28
/FTDI_PWREN: R83.2, U81.10, U82.12
/FTDI_RD: U81.12, U82.13
/FTDI_RXF: U81.15, U82.23
/FTDI_TXE: U81.14, U82.22
/FTDI_WR: U81.13, U82.14
/JTAG_TCK: JTAG1.1, R15.1, U81.26
/JTAG_TDI: JTAG1.9, R17.2, U81.1
/JTAG_TDO: JTAG1.3, U81.32
/JTAG_TMS: JTAG1.5, R16.2, U81.7
/USB_CS: U81.34, X3.3
/USB_RD: U81.35, X3.4
/USB_SPARE1: U81.38, X3.6
/USB_SPARE2: LEDG1.2, U81.37, X3.2
GND: C15.2, C16.2, C81.2, C82.2, C83.2, C84.2, C85.2, C86.2, C87.2, C88.2, JTAG1.2, JTAG1.10, R15.2, R82.1, R91.1, R92.1, U5.1, U81.4, U81.11, U81.16, U81.24, U81.30, U81.36, U82.7, U82.18, U82.21, U82.25, U82.26, X1.GND, X3.1, X3.5, X3.10
unnamed: C84.1, U82.17
unnamed: JP2.1, R81.2, X1.VBUS
unnamed: LEDG1.1, R92.2
unnamed: LEDR1.1, R91.2
unnamed: R81.1, R82.2, U82.19
unnamed: U82.15, X1.D+
unnamed: U82.16, X1.D-

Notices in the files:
board/wasca.kicad_pcb:
Distributed under GNU GENERAL PUBLIC LICENSE Version 2
